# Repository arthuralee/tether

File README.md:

# Tether

## Tether provides real-time tracking of physical objects.
Tether tracks the orientation and position of an object in 3D space, making the data available for use in the construction of a 3D world.

http://www.ece.cmu.edu/~ece549/spring15/team05/

This is our project repository, which will contain code for all parts of the project.

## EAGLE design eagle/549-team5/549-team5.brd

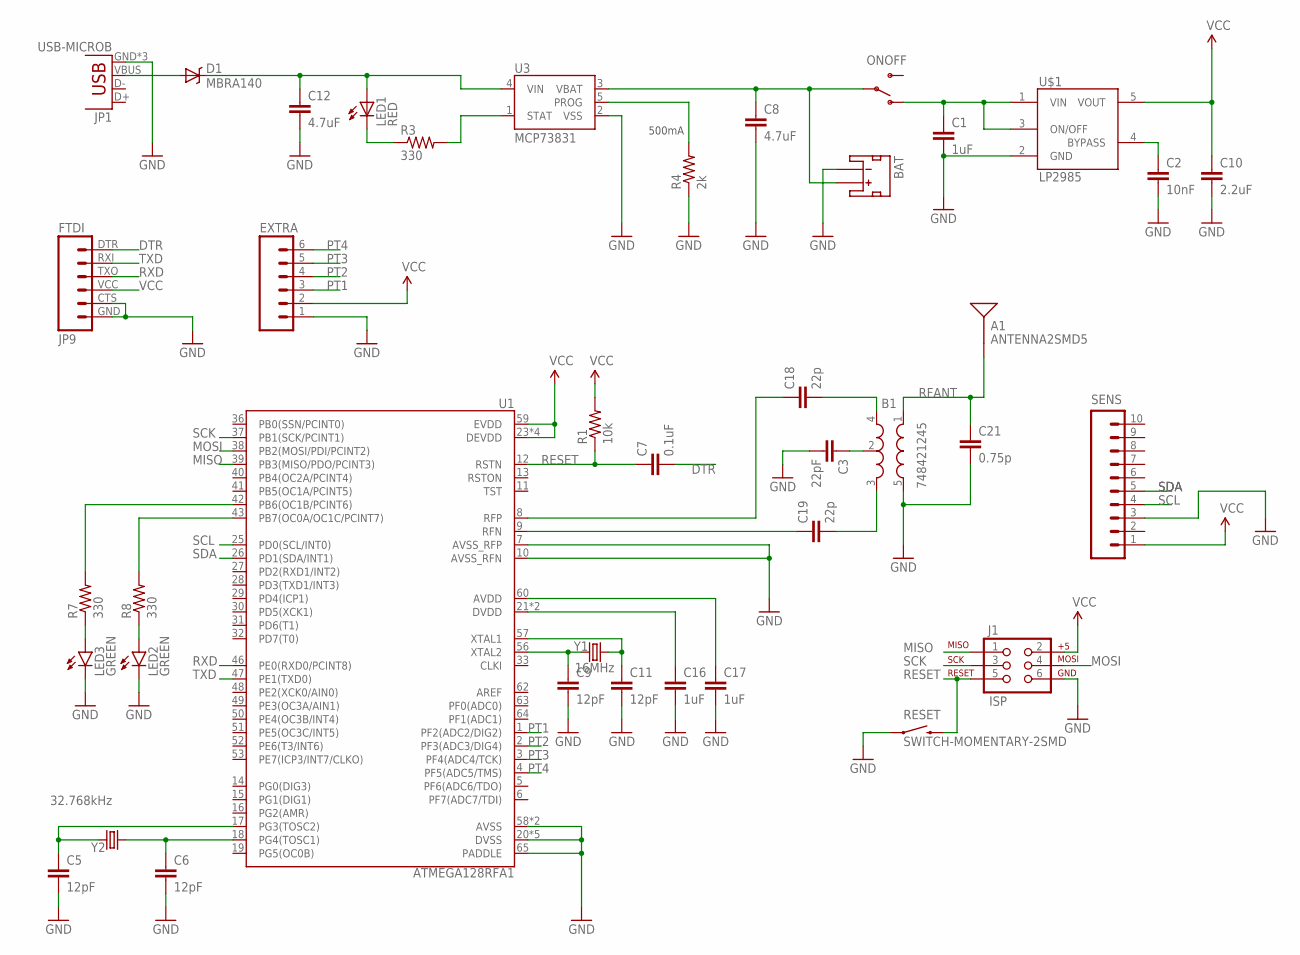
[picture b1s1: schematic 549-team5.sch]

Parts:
A1: ANTENNA2SMD5; ANTENNA-CHIP5
B1: 748421245; BALUN
BAT: JST_2MM_MALE; JST-2-SMD
C1, C16, C17: 1uF; 1206
C2: 10nF; 1206
C3: 22pF; 1206
C5, C6, C9, C11: 12pF; 1206
C7: 0.1uF; 1206
C8, C12: 4.7uF; 1206
C10: 2.2uF; 1206
C18, C19: 22p; 1206
C21: 0.75p; 1206
D1: MBRA140; SMA-DIODE
EXTRA: M06SILK_FEMALE_PTH; 1X06
J1: ISP; 2X3-NS
JP1: USB-MICROB
JP9: FTDI; FTDI_BASIC
LED1: RED; LED-1206
LED2, LED3: GREEN; LED-1206
ONOFF: SWITCH-SPST-SMD-A
R1: 10k; 1206
R3, R7, R8: 330; 1206
R4: 2k; 1206
RESET: SWITCH-MOMENTARY-2SMD; TACTILE-SWITCH-SMD
SENS: M10SILK_FEMALE_PTH; 1X10
U1: ATMEGA128RFA1; QFN-64
U3: MCP73831; SOT23-5
U$1: LP2985AIM5-3.3; SOT25
Y1: 16MHz; CRYSTAL-SMD-5X3
Y2: 32.768kHz; CRYSTAL-32KHZ-SMD

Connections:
AVDD: C17.1, U1.60 (AVDD)
BYPASS: C2.1, U$1.4 (BYPASS)
DTR: C7.2, JP9.DTR (1)
DVDD: C16.1, U1.21 (DVDD), U1.22 (DVDD)
GND: B1.5 (GND), BAT.1 (-), C1.2, C2.2, C3.2, C5.2, C6.2, C8.2, C9.2, C10.2, C11.2, C12.2, C16.2, C17.2, C21.2, EXTRA.1, J1.6, JP1.GND, JP1.MT1 (GND), JP1.MT2 (GND), JP9.CTS (5), JP9.GND (6), LED2.C, LED3.C, R4.1, RESET.1, SENS.3, U1.7 (AVSS_RFP), U1.10 (AVSS_RFN), U1.20 (DVSS), U1.24 (DVSS), U1.35 (DVSS), U1.45 (DVSS), U1.55 (DVSS), U1.58 (AVSS), U1.61 (AVSS), U1.65 (PADDLE), U3.2 (VSS), U$1.2 (GND)
MISO: J1.1, U1.39 (PB3(MISO/PDO/PCINT3))
MOSI: J1.4, U1.38 (PB2(MOSI/PDI/PCINT2))
unnamed: R8.2, U1.43 (PB7(OC0A/OC1C/PCINT7))
unnamed: C11.1, U1.57 (XTAL1), Y1.3 (2)
unnamed: C9.1, U1.56 (XTAL2), Y1.1
unnamed: C6.1, U1.18 (PG4(TOSC1)), Y2.X1 (1)
unnamed: C5.1, U1.17 (PG3(TOSC2)), Y2.X2 (2)
unnamed: C1.1, ONOFF.1 (O), U$1.1 (VIN), U$1.3 (ON/OFF)
unnamed: LED3.A, R7.1
unnamed: BAT.2 (+), C8.1, ONOFF.2, U3.3 (VBAT)
unnamed: B1.4 (OUT1), C18.2
unnamed: B1.3 (OUT2), C19.2
unnamed: R7.2, U1.42 (PB6(OC1B/PCINT6))
unnamed: LED2.A, R8.1
unnamed: B1.2 (GND), C3.1
unnamed: C12.1, D1.C, LED1.A, U3.4 (VIN)
unnamed: R3.2, U3.1 (STAT)
unnamed: LED1.C, R3.1
unnamed: D1.A, JP1.VBUS
PROG: R4.2, U3.5 (PROG)
PT1: EXTRA.3, U1.1 (PF2(ADC2/DIG2))
PT2: EXTRA.4, U1.2 (PF3(ADC3/DIG4))
PT3: EXTRA.5, U1.3 (PF4(ADC4/TCK))
PT4: EXTRA.6, U1.4 (PF5(ADC5/TMS))
RESET: C7.1, J1.5, R1.1, RESET.3 (2), U1.12 (RSTN)
RFANT: A1.FEED, B1.1 (IN), C21.1
RFN: C19.1, U1.9 (RFN)
RFP: C18.1, U1.8 (RFP)
RXD: JP9.TXO (3), U1.46 (PE0(RXD0/PCINT8))
SCK: J1.3, U1.37 (PB1(SCK/PCINT1))
SCL: SENS.4, U1.25 (PD0(SCL/INT0))
SDA: SENS.5, U1.26 (PD1(SDA/INT1))
TXD: JP9.RXI (2), U1.47 (PE1(TXD0))
VCC: C10.1, EXTRA.2, J1.2, JP9.VCC (4), R1.2, SENS.1, U1.23 (DEVDD), U1.34 (DEVDD), U1.44 (DEVDD), U1.54 (DEVDD), U1.59 (EVDD), U$1.5 (VOUT)

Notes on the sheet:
500mA

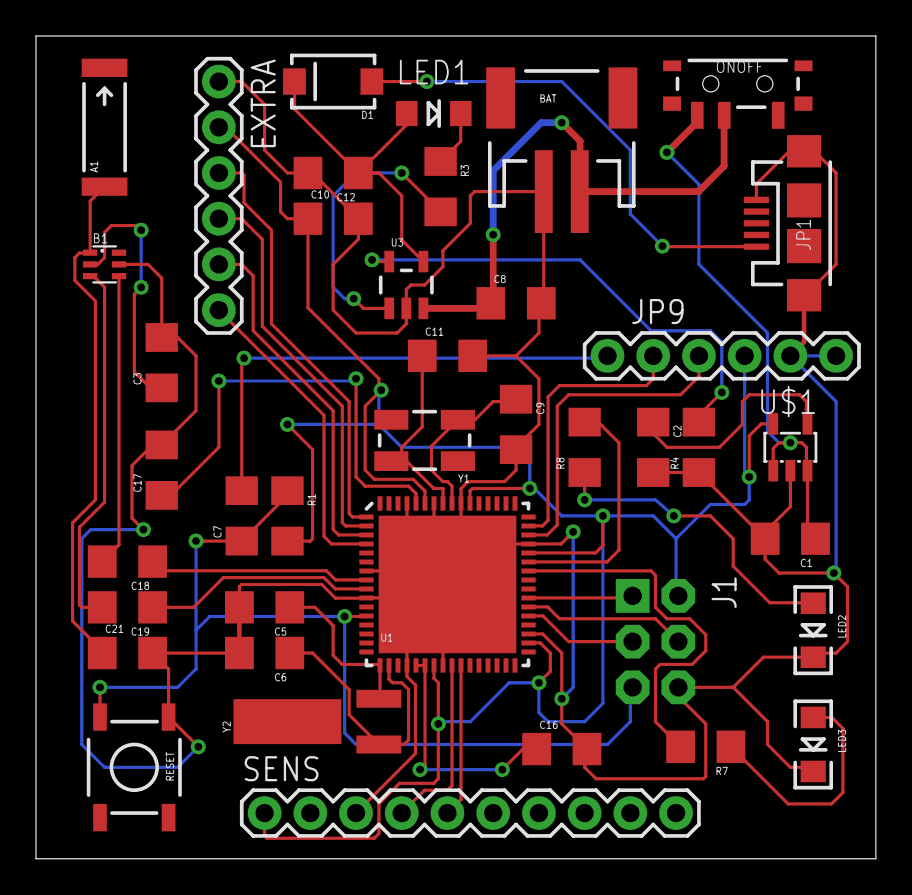
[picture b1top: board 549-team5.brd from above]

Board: 2 copper layers, 46.7 x 45.7 mm, 40 parts (0 on the bottom side), 39 nets.

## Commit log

2015-04-06 Added apriltags server code
2015-04-06 Fixed gitignore
2015-04-06 Added unity-pos, TCP client for position
2015-04-06 Added eagle files
2015-04-06 Added readme
2015-04-06 Added website
2015-04-06 Removed extra image in root
2015-04-06 Added media with pics of schematic and board
2015-04-19 arduino code, libraries and main
2015-04-20 Added cpp versions of arduino code with Makefile
2015-04-27 sensor data and filter in unity c#
2015-04-29 [tether-cam] Fixed case for TCP files
2015-05-01 wireless!
2015-05-01 Updated sensor printing
2015-05-02 Added support for stopping and starting server
2015-05-02 rotation 3d
2015-05-02 Fixed bug in apriltags code
2015-05-02 Added button code for PCB
2015-05-02 Updated moveCube to match new apriltags
2015-05-02 Lowered delay to 20ms
2015-05-02 Adafruit_9dof library updated getFusionSensor
2015-05-02 Re-patched 9DOF lib
2015-05-06 Added serial port server
2015-05-06 Fixed robustness for serialServer
2015-05-06 Fixed SO_REUSEADDR
2015-05-11 Added poster
2015-05-13 Added video embed to website

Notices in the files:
parts and their libraries:
SparkFun-RF: Licensing: CC v3.0 Share-Alike You are welcome to use this library for commercial purposes.
SparkFun-Capacitors: Licensing: Creative Commons ShareAlike 4.0 International - https://creativecommons.org/licenses/by-sa/4.0
